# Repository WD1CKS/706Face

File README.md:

# 706Face - An IC-706 Head Unit Emulator

This project is to develop a head unit emulator and replacement CAT system for the IC-706.

## Hardware

Firmware is being written for the Raspberry Pi Pico.

## Features

Planned feature list:
* Kenwood-style CAT on the USB stdio port
* Integrated FSK keyer
* Integrated CW keyer
* Custom designed control panel using consumer parts (ie: Cherry MX switches, arcade spinners, etc)
* Small LCD display
* Full functionality of stock head unit

## References

https://www.oz9aec.net/radios/ic-706/diy-remote-kit-for-the-ic-706-part-2-a-closer-look-at-the-protocol
https://ok1zia.nagano.cz/wiki/Front_panel_IC-706

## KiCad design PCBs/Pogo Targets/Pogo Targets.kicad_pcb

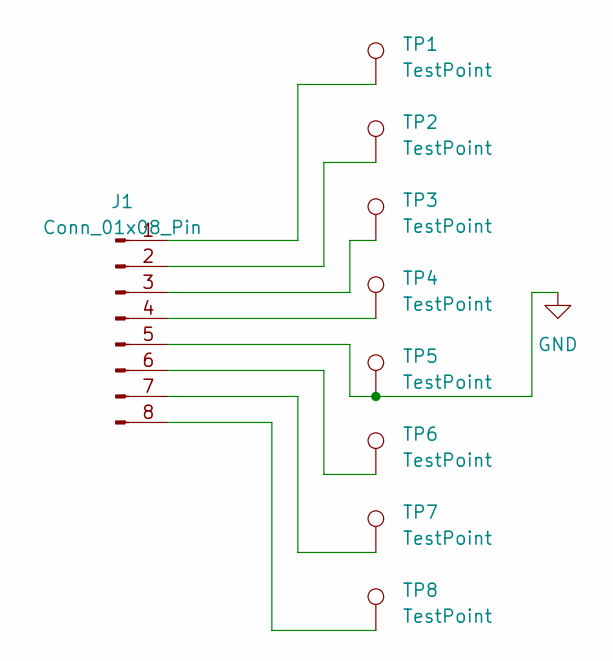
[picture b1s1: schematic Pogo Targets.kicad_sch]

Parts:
J1: Conn_01x08_Pin; PinHeader_1x08_P2.54mm_Vertical
TP1, TP2, TP3, TP4, TP5, TP6, TP7, TP8: TestPoint; TestPoint_Pad_D1.5mm

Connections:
GND: J1.5, TP5.1
unnamed: J1.1, TP1.1
unnamed: J1.2, TP2.1
unnamed: J1.3, TP3.1
unnamed: J1.4, TP4.1
unnamed: J1.6, TP6.1
unnamed: J1.7, TP7.1
unnamed: J1.8, TP8.1

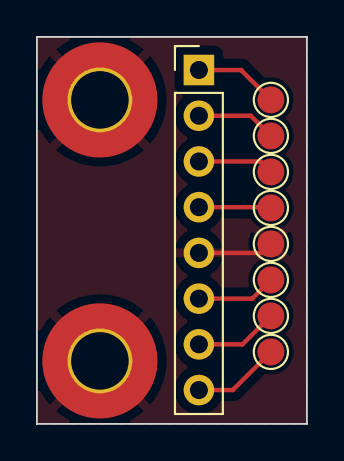
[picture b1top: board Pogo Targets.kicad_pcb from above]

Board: 2 copper layers, 15.0 x 21.5 mm, 9 parts (0 on the bottom side), 8 nets.

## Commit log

2024-05-23 Add README.md
    Just bread strokes of the project at this point.
2024-05-23 Add references
2024-05-23 Add summary of references
    In case the web sites go away.
2024-05-23 Fix typo
2024-05-23 Use "Head unit" instead of "faceplate"
2024-05-23 Add some boilerplate and initial hackery
    Currently does nopthing forever.
2024-05-23 Document the connector as well.
2024-05-23 Mention it's a single row of eight pins
2024-05-23 Add KiCad for Pogo Targets
2024-05-23 Add utility to hack the Gibson.
2024-05-23 Ignore STEP files in PCBs too
    So I can 3D print them to prototype fitment.
2024-05-24 Ignore _autosave- from kicad as well.
2024-05-24 Start CADding up some stuff.
2024-05-24 Some fitment tweaks.
    Bottom piece didn't engage fully, top plate hole spacing was off.
2024-05-24 Fix some typos.
2024-05-24 Some notes on how to connect the pico
2024-05-24 Add section on power
2024-05-24 Mention the required Schottky.
2024-05-25 Document using PIO for keying
2024-05-25 Fiddle with clips, add the rest of the parts.
    Still need to figure out board mounting, but we should really have
    boards before we do that.
2024-05-26 Final tweakage... can not be printed and assembled.
    Still needs PCB mounts and cable strain relief.
2024-05-26 Add initial STLs.
    This was used for prototype fitment, no cable strain relief or PCB
    mount posts yet.
2024-05-26 Fix part orientation for printing.
2024-05-26 Start of the pass-through plate.
    Does not yet have the pogo pins to make the electrical connection.
